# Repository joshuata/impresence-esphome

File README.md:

# Presence Sensor

An open-source, ESPHome-based room presence sensor built around the Hi-Link HLK-LD2460 mmWave radar and a Seeed Studio XIAO ESP32-S3. The base device detects human presence, even when people are sitting still, and reports it to Home Assistant. Optional add-ons extend it with ambient light and CO₂ sensing.

> **Status:** early development. Hardware and firmware are not yet finalized.

<!-- TODO: hero photo of the assembled device -->

## Features

- mmWave presence detection (HLK-LD2460)
- Native Home Assistant integration through ESPHome
- Wi-Fi setup over USB or Bluetooth (Improv), with no code editing required
- Browser-based flashing, no toolchain needed
- Over-the-air updates
- Optional add-ons:
  - Ambient light sensor
  - CO₂ sensor
- Custom PCB and 3D-printable enclosure, with source files included

## Bill of materials

### Base device

| Qty | Part | Notes |
|----:|------|-------|
| 1 | Seeed Studio XIAO ESP32-S3 | |
| 1 | Hi-Link HLK-LD2460 mmWave radar | |
| 1 | Custom PCB | See [`hardware/pcb`](hardware/pcb) |
| 1 | 3D-printed enclosure | See [`hardware/enclosure`](hardware/enclosure) |
| 1 | USB-C cable + 5 V power supply | |
| 1 | PCB parts (radar sockets, Qwiic socket, LDO, passives) | Full list in [`hardware/pcb/presence-pcb-bom.csv`](hardware/pcb/presence-pcb-bom.csv) |
| 4 | M2.5 screws + heat-set inserts | Length TBD with the case |

### Optional add-ons

| Add-on | Part | Notes |
|--------|------|-------|
| Ambient light | Adafruit VEML7700 Lux Sensor, STEMMA QT (5378) | Plugs into the Qwiic chain |
| CO₂ | Adafruit SCD-40 breakout (5187) | Plugs into the Qwiic chain |

## Building

### 1. PCB

TODO: ordering the PCB from fabrication files, assembly notes, soldering order.

### 2. Enclosure

TODO: print settings (material, layer height, supports, infill) and orientation.

### 3. Assembly

TODO: mounting the PCB, radar orientation, and installing add-ons.

## Flashing

### Option A: Browser (recommended)

TODO: link to the ESP Web Tools install page. Connect the device over USB, click **Install**, then enter your Wi-Fi credentials when prompted.

### Option B: ESPHome Dashboard / CLI

Requires ESPHome TBD or newer, the first release with the [`ld2460`](https://next.esphome.io/components/sensor/ld2460/) component.

```bash
pip install esphome
esphome run firmware/presence.yaml
```

TODO: adopting the device in the ESPHome Dashboard.

## Wi-Fi setup

TODO: Improv over serial/BLE and fallback access point instructions.

## Home Assistant

TODO: discovery, exposed entities, and suggested automations.

## Enabling add-ons

TODO: how to include the add-on packages in `firmware/presence.yaml`.

## Repository layout

| Path | Contents |
|------|----------|
| `firmware/` | ESPHome configuration and add-on packages |
| `hardware/pcb/` | Autodesk Fusion PCB design and fabrication exports |
| `hardware/enclosure/` | Autodesk Fusion enclosure design and printable files |
| `docs/` | Images, wiring diagrams, web installer |

## Made for ESPHome

This project aims to meet the [Made for ESPHome](https://esphome.io/guides/made_for_esphome/) requirements. Progress against the [checklist](https://github.com/esphome/devices.esphome.io/blob/main/.github/made-for-esphome-checklist.md) is tracked in the project issues.

## Contributing

Issues and pull requests are welcome. If you use an AI coding agent, it should follow [`AGENTS.md`](AGENTS.md).

## License

- **Firmware, software, and documentation:** [GNU General Public License v3.0 or later](LICENSE) (`GPL-3.0-or-later`).
- **Hardware designs** (everything under `hardware/`: PCB, enclosure, and their fabrication exports): [CERN Open Hardware Licence v2 – Strongly Reciprocal](LICENSE-HARDWARE) (`CERN-OHL-S-2.0`).

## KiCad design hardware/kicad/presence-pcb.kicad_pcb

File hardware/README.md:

# Hardware

The Autodesk Fusion project **Presence sensor** holds the mechanical source designs; Fusion exports are kept here so they are version controlled and usable without Fusion. The main PCB is a KiCad project in this folder (see `AGENTS.md`, Hardware).

| Path | Contents |
|------|----------|
| `fusion/` | Fusion source exports (`.f3d`; `.f3z` for designs with inserted, referenced components) |
| `kicad/` | KiCad 10 project for the main PCB: schematic, board, project symbol/footprint library and build scripts |
| `pcb/` | Fabrication outputs for the main PCB: Gerber + drill zip, BOM, JLCPCB assembly files |
| `enclosure/` | Print outputs for the case (once finalized) |

## Designs

| Design | What it is |
|--------|------------|
| `ld2460 Board` | HLK-LD2460 radar: board, headers, pins, keep-outs |
| `xiao-esp32s3` | Seeed XIAO ESP32-S3: board, pin holes, USB-C, keep-out |
| `adafruit-scd40` | Adafruit SCD-40 breakout (for later case variants) |
| `adafruit-veml7700` | Adafruit VEML7700 breakout (for later case variants) |
| `presence-skeleton` | Master layout for the radar + PCB prototype. Derives the radar and XIAO models and holds every case, PCB, mount and antenna dimension. All user parameters are Favourites so other designs can derive them |
| `presence-enclosure` | Case v1: base and press-fit cover. Derives the skeleton's parameters (`_Ref`), layout sketches and reference bodies |

## Changing dimensions

The dimensions you're likely to change are named user parameters, and most others are derived from them or from the component models. In Fusion, open `presence-skeleton` and go to **Modify → Change Parameters**. Edit the value in the *User Parameters* section, and everything that depends on it updates. Parameters ending in `_Ref` come from the component models; change those in the component design instead. The case derives from the skeleton, so changes made there flow through to it. The KiCad PCB takes its outline, holes and part positions from the same values (in `kicad/scripts/build_board.py`), so update the script and rebuild the board after changing a layout parameter.

Values most people will want to check before printing are **bold**.

### Layout

| Parameter | Value | Description |
|-----------|-------|-------------|
| `pcb_thickness` | 1.6 mm | Main PCB thickness |
| **`pcb_socket_h`** | 4.3 mm | Height of the 2.0 mm female sockets the radar plugs into. Set to the part you buy |
| `pcb_margin` | 2 mm | PCB extends this far beyond the radar outline |
| `pcb_hole_inset` | 3 mm | PCB edge to mounting-hole centre |
| `pcb_pin_protrusion` | 2 mm | Through-hole pin length below the PCB |
| `layout_gap_radar_xiao` | 3 mm | Gap between the radar outline and the top of the XIAO |
| `xiao_side_offset` | 10 mm | XIAO shifted right (toward the antenna) to leave room on the left for a right-angle USB-C plug |

### Case

| Parameter | Value | Description |
|-----------|-------|-------------|
| `case_wall` | 2 mm | Wall thickness |
| `case_corner_r` | 3 mm | Outer corner radius |
| `case_margin` | 1 mm | Clearance from the PCB edge to the inner wall |
| **`case_radome_t`** | 1.4 mm | Wall thickness in front of the radar (community reports for 24 GHz; verify with a range test) |
| **`case_radome_gap`** | 2 mm | Radar antenna face to the inside of the front wall (1–3 mm) |
| **`case_bay_h`** | 12.5 mm | Cable bay below the PCB; sized for a right-angle USB-C plug |
| **`tol_clearance`** | 0.2 mm | General clearance between printed parts; tune for your printer |

### Fasteners

| Parameter | Value | Description |
|-----------|-------|-------------|
| `screw_clear_d` | 2.7 mm | M2.5 clearance hole in the PCB |
| **`insert_hole_d`** | 3.6 mm | Heat-set insert hole diameter. Inserts vary by brand; use your supplier's recommendation |
| **`insert_hole_h`** | 4 mm | Heat-set insert hole depth |
| `insert_boss_d` | 6.5 mm | Boss diameter around each insert |

### Wall mount (keyholes)

The back has two keyholes on the vertical centreline. Any accessory, such as a wedge or stand, that presents two #8 pan-head screw heads (or printed studs of the same shape) at this spacing can hold the case.

| Parameter | Value | Description |
|-----------|-------|-------------|
| **`mount_head_d`** | 7.9 mm | #8 pan-head diameter (ASME B18.6.3 nominal; measure yours) |
| **`mount_head_h`** | 2.8 mm | #8 pan-head height (nominal; measure yours) |
| `mount_shank_d` | 4.2 mm | #8 shank diameter |
| `mount_keyhole_spacing` | 40 mm | Keyhole centre-to-centre |
| `mount_slot_len` | 8 mm | Slot length above each entry hole |

### Hinge

Not used by case v1 (press-fit cover); kept in the skeleton for later variants.

| Parameter | Value | Description |
|-----------|-------|-------------|
| **`hinge_pin_d`** | 1.75 mm | Hinge pin: a piece of 1.75 mm filament or a metal pin |
| `hinge_knuckles` | 5 | Number of hinge knuckles |
| `hinge_clearance` | 0.3 mm | Knuckle and pin clearance |

### Wi-Fi / Bluetooth antenna

The XIAO's included flexible antenna sticks flat to the inside of the right-hand side wall. Its U.FL cable makes a 180° U-bend before reaching the XIAO, to take strain off the antenna joint.

| Parameter | Value | Description |
|-----------|-------|-------------|
| `ant_len` × `ant_w` × `ant_t` | 37.5 × 17.5 × 0.25 mm | Antenna size (measured) |
| `ant_cable_len` | 60 mm | U.FL cable length (measured) |
| `ant_bend_gap` | 6 mm | Spacing of the U-bend |
| `ant_drop` | 5 mm | Antenna centre below the radar centreline |
| `xiao_ufl_from_edge`, `xiao_ufl_from_centre` | 1.72, 4.73 mm | U.FL connector position on the XIAO (from Seeed's 3D model) |

### USB cable

| Parameter | Value | Description |
|-----------|-------|-------------|
| `usb_plug_w` × `usb_plug_h` | 12 × 6.5 mm | Straight USB-C plug body (measure your cable) |
| `usb_cable_d` | 4 mm | Cable diameter |
| `usb_cable_bend_r` | 10 mm | Minimum bend radius |

### Derived values (don't edit)

| Parameter | Value | Meaning |
|-----------|-------|---------|
| `z_antenna_face` | 8.0 mm | Radar antenna face above the PCB front |
| `case_front_inner` | 10.0 mm | Inside of the front wall above the PCB front |
| `pcb_back_clear` | 6.3 mm | Space behind the PCB: the largest of pin clearance, insert depth and the depth the antenna needs |
| `case_inner_depth` | 17.9 mm | Inside depth of the case |
| `case_inner_half_w`, `case_inner_top`, `case_inner_bottom` | 27.75, 19.0, 52.455 mm | Inner case extents from the radar centre |
| `ant_path_len` | 44.2 mm | Estimated antenna cable route |
| `ant_path_slack` | 15.8 mm | Spare cable. **Must stay ≥ 0**; adjust `ant_drop` if it goes negative |

At these values the case is about 59.5 × 75.5 × 21.3 mm (W × H × D).

## Main PCB

KiCad project `kicad/presence-pcb.kicad_pro`; two layers, 53.5 × 57.955 mm, 1.6 mm. The outline, the four M2.5 holes, the radar sockets and the XIAO position come from `presence-skeleton` (radar centre = origin, PCB front facing the room). Every part is on the front; the back carries only through-hole pins and a GND pour.

### Rebuilding

```sh
cd hardware/kicad
kicad-cli sch export netlist --format kicadsexpr -o /tmp/presence.net presence-pcb.kicad_sch
"/Applications/KiCad/KiCad.app/Contents/Frameworks/Python.framework/Versions/Current/bin/python3" \
  scripts/build_board.py /tmp/presence.net      # placement, routing, pours, silkscreen
scripts/export_fab.sh                           # ERC + DRC + parity, then hardware/pcb/*
```

`build_board.py` routes with its own small grid router, so the board is reproducible from the schematic without an autorouter. The custom footprints in `presence.pretty` come from `scripts/gen_footprints.py`.

### Wiring

Nets are named after XIAO pins. These match `firmware/boards/xiao-esp32s3.yaml`.

| Net | XIAO pin | Goes to |
|-----|----------|---------|
| `D8` | D8 (TX) | LD2460 J1 pin 8, Rx2 |
| `D9` | D9 (RX) | LD2460 J1 pin 7, Tx2 |
| `D4` | D4 (SDA) | Qwiic J3 pin 3, J4 pin 3 |
| `D5` | D5 (SCL) | Qwiic J3 pin 4, J4 pin 4 |
| `5V` | 5V (VBUS) | Radar filter, Qwiic LDO, hardwired input diode |
| `RADAR_5V` | – | LD2460 JP103 pin 1, after FB1 + 22 µF + 100 nF |
| `QWIIC_3V3` | – | Qwiic J3/J4 pin 2, from the AP2112K LDO U2 |
| `GND` | GND | LD2460 pins 2 and 6, Qwiic pin 1 |
| `D0` `D1` `D3` `D6` `D7` `D10` | spare | Test pads TP1–TP6 (through-hole, wire-solderable). D2 is left unconnected: GPIO3 is an S3 strapping pin |

LD2460 pin numbers follow manual V1.1, Fig. 3. The PCB faces the module's component side, so the socket footprints are mirrored relative to that photo: on the PCB, JP103 pin 1 (5 V) is the bottom pin of the column nearest the board edge, and J1 pin 5 is the bottom pin of the inner column. **Check the first board against a module before powering it.**

### Parts

`pcb/presence-pcb-bom.csv` lists every part. `pcb/presence-pcb-bom-jlcpcb.csv` and `pcb/presence-pcb-cpl-jlcpcb.csv` are for JLCPCB assembly: they include the SMD parts, the radar sockets and the Qwiic socket, and leave out the XIAO (hand-soldered) and the DNP parts. Check the part rotations in JLCPCB's placement preview before ordering.

- **XIAO (U1):** solder it flush (castellated edges onto the pads) or on pin headers. The footprint uses the 14 edge pins only; there is no copper on the front under the XIAO's bottom pads.
- **Radar sockets (J1, J2):** 2.0 mm female, 4.3 mm tall (`pcb_socket_h`). The radar plugs in with its antennas facing out.
- **Qwiic (J3):** JST SH BM04B-SRSS-TB, top entry (the cable plugs in from the front), body centre at (-22.8, -27.5) skeleton coordinates, 3.45 mm in from the left PCB edge. The header is 4.25 mm tall and the SHR-04V-S plug housing is 5 mm tall (JST SH catalogue eSH, pp. 2–3); JST gives no mated height, so measure a real cable before finalizing the cover. J4 is the same bus on 2.54 mm pads for a soldered cable or header. Both are fed 3.3 V by a dedicated AP2112K-3.3 LDO (U2), separate from the XIAO's 3V3.
- **I²C pull-ups (R1, R2, DNP):** the Adafruit breakouts have their own. Fit 4.7 kΩ only for a breakout without pull-ups.
- **Hardwired 5 V (J5, DNP):** 2-pin 2.54 mm pads at the bottom edge for bare 5 V wires, feeding VBUS through an SS34 Schottky (D1). The XIAO's 5V pin is wired straight to its USB VBUS (XIAO ESP32S3 schematic v1.4), so D1 stops USB from back-feeding the hardwired supply, but not the reverse: a hardwired supply more than about 0.3 V above USB VBUS would feed the USB host. Unplug the hardwired supply before connecting USB to a computer.
- **Antenna side:** no copper pour within 5.5 mm of the right edge, next to the antenna on the side wall.

## Case v1 (`presence-enclosure`)

A plain box in two printed parts:

- **Base:** back wall, four side walls, M2.5 heat-set insert bosses for the PCB, two keyholes with head pockets (mount interface above), the antenna pocket on the inside of the right wall, and a U-bend guide post for the antenna cable below it.
- **Cover:** the flat radome (`case_radome_t`), with a lip that drops inside the base. The left and right lips are a press fit (`case_press_fit`) with a lead-in chamfer; the top and bottom lips only locate. The right lip stops below the antenna so it never presses on it. Pry the cover off at the seam.
- **Edges:** a small 45° chamfer (`case_edge_chamfer`) on the front and back outer edges; nothing else sticks out.
- **Cable exits:** four options, each switched on or off with a parameter (1/0). Disabled cutters are moved out of the part, so the timeline stays healthy either way.

| Exit | Parameter | Default | What it is |
|------|-----------|---------|------------|
| Bottom | `exit_bottom` | 1 | Opening for a straight USB-C plug body (`usb_plug_w` × `usb_plug_h` + clearance) through the bottom wall, in line with the XIAO's USB-C |
| Left / right | `exit_left`, `exit_right` | 0 | U-slot for the cable (`usb_cable_d`) from the wall top, at the bay floor; the cover closes it. Strain-relief ribs pinch the cable by `exit_grip` |
| Back | `exit_back` | 0 | Hole for the cable (`usb_cable_d`) through the back wall into the wall cavity, with strain-relief ribs. Thread the far end through first |

Enclosure parameters (in `presence-enclosure`, **Modify → Change Parameters**):

| Parameter | Value | Description |
|-----------|-------|-------------|
| **`case_press_fit`** | 0.1 mm | Interference per side between the cover's side lips and the base walls. Tune for your printer; 0 = slip fit |
| `case_lip_h` | 2 mm | Cover lip height into the base |
| `case_lip_t` | 1.2 mm | Cover lip thickness |
| `case_edge_chamfer` | 0.8 mm | Chamfer on the front and back outer edges. Must stay below `case_radome_t` |
| `mount_hood_roof` | 1 mm | Roof over each keyhole head pocket. Above ~1.2 mm it reaches the through-hole pins behind the PCB |
| `ant_cable_d` | 1.13 mm | U.FL pigtail coax diameter (sizes the U-bend guide post); measure yours |
| `exit_grip` | 0.4 mm | How much the strain-relief ribs pinch the cable |
| `exit_bottom`, `exit_left`, `exit_right`, `exit_back` | 1, 0, 0, 0 | Cable exit toggles (see above) |
| `case_back_z`, `case_front_z`, `case_outer_half_w` | 9.9, 11.4, 29.75 mm | Derived; don't edit |

### Printing

`enclosure/presence-enclosure.3mf` is an OrcaSlicer project with both parts in print orientation: the base on its back, the cover radome-down. Neither needs supports (the keyhole pocket roofs and the bottom exit opening are short bridges; the edge chamfers are 45°). The embedded settings:

| Setting | Value |
|---------|-------|
| Printer profile | Bambu Lab A1 0.4 nozzle (any 0.4 mm printer works; switch it in the slicer and keep the process) |
| Material | PLA (Generic PLA). PETG also works; check radar range through the radome |
| Layer height | 0.2 mm (first layer 0.2 mm) |
| Walls | 3 |
| Top / bottom layers | 5 / 4 |
| Infill | 20 % gyroid |
| Supports | Off |
| Brim | Off |

`enclosure/presence-enclosure.step` holds both parts assembled (cover closed) for anyone who wants to modify them.

### Assembly

1. Press M2.5 heat-set inserts into the four bosses.
2. Stick the antenna into its pocket, run the cable down around the guide post and back up to the XIAO's U.FL.
3. Screw the PCB onto the inserts, plug in the cable and route it out of the enabled exit.
4. Press the cover on.

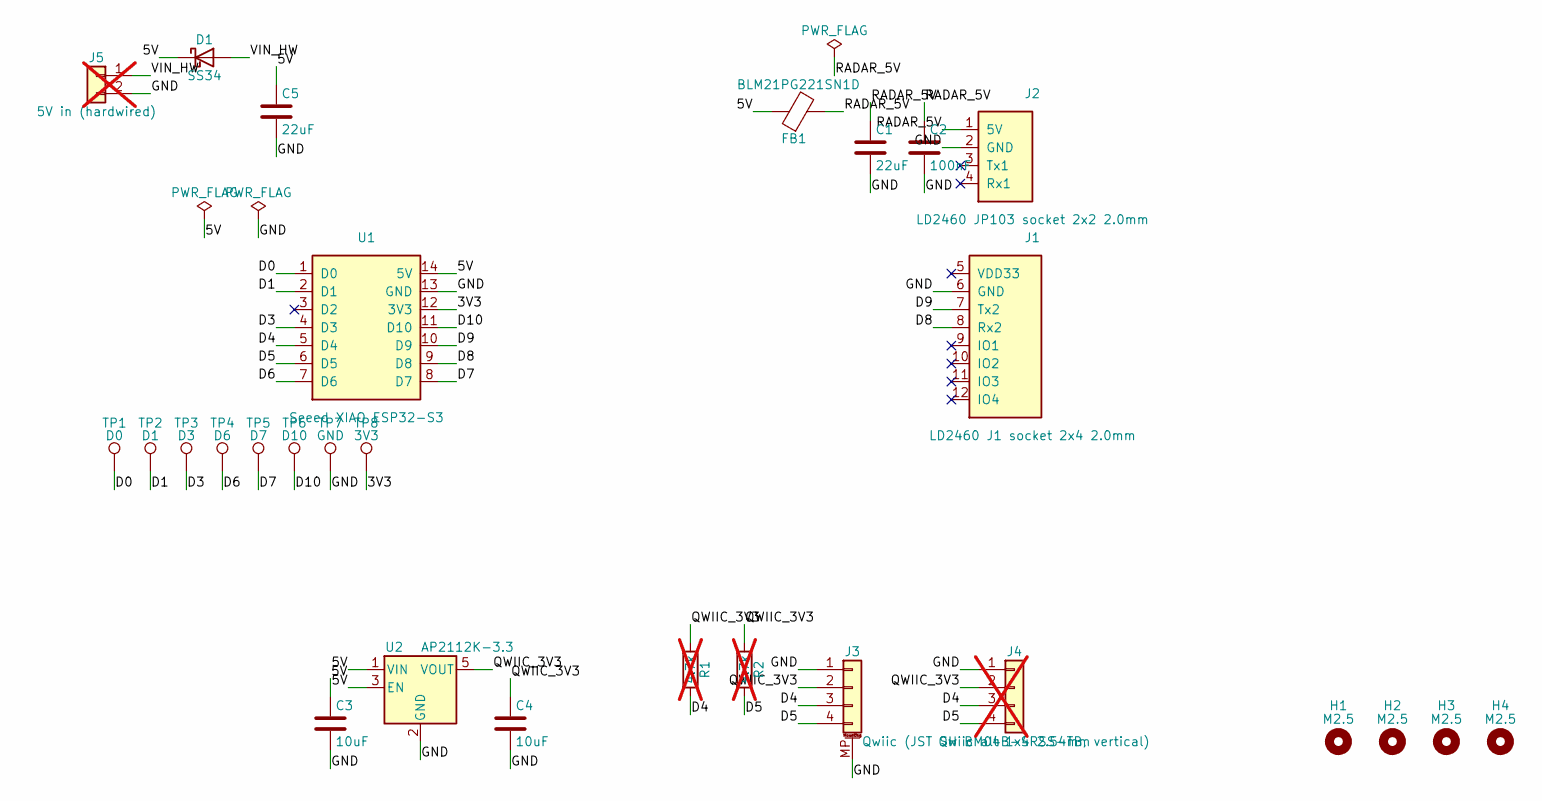
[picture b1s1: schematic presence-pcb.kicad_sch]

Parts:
C1, C5: 22uF; C_0805_2012Metric; MPN CL21A226MAQNNNE; LCSC C45783
C2: 100nF; C_0805_2012Metric; MPN CC0805KRX7R9BB104; LCSC C49678
C3, C4: 10uF; C_0805_2012Metric; MPN CL21A106KAYNNNE; LCSC C15850
D1: SS34; D_SMA; MPN SS34; LCSC C8678
FB1: BLM21PG221SN1D; L_0805_2012Metric; MPN BLM21PG221SN1D; LCSC C85840
H1, H2, H3, H4: M2.5; MountingHole_2.7mm_M2.5
J1: LD2460 J1 socket 2x4 2.0mm; LD2460_J1_Socket_2x04_P2.00mm; MPN PM200-2-04-Z-4.3; LCSC C2906072
J2: LD2460 JP103 socket 2x2 2.0mm; LD2460_JP103_Socket_2x02_P2.00mm; MPN PM200-2-02-Z-4.3; LCSC C2906070
J3: Qwiic (JST SH BM04B-SRSS-TB, vertical); JST_SH_BM04B-SRSS-TB_1x04-1MP_P1.00mm_Vertical; MPN BM04B-SRSS-TB(LF)(SN); LCSC C160390
J4: Qwiic alt 1x4 2.54mm; PinHeader_1x04_P2.54mm_Vertical; MPN 1x4 2.54 mm pin header; not fitted
J5: 5V in (hardwired); PinHeader_1x02_P2.54mm_Vertical; MPN 1x2 2.54 mm pin header or 2-pin 2.54 mm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; not fitted
R1, R2: 4.7k; R_0805_2012Metric; MPN 0805W8F4701T5E; LCSC C17673; not fitted
TP1: D0; TestPoint_THTPad_D1.5mm_Drill0.7mm
TP2: D1; TestPoint_THTPad_D1.5mm_Drill0.7mm
TP3: D3; TestPoint_THTPad_D1.5mm_Drill0.7mm
TP4: D6; TestPoint_THTPad_D1.5mm_Drill0.7mm
TP5: D7; TestPoint_THTPad_D1.5mm_Drill0.7mm
TP6: D10; TestPoint_THTPad_D1.5mm_Drill0.7mm
TP7: GND; TestPoint_THTPad_D1.5mm_Drill0.7mm
TP8: 3V3; TestPoint_THTPad_D1.5mm_Drill0.7mm
U1: Seeed XIAO ESP32-S3; XIAO_ESP32S3_EdgePins; MPN XIAO ESP32S3
U2: AP2112K-3.3; SOT-23-5; MPN AP2112K-3.3TRG1; LCSC C51118

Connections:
/3V3: TP8.1, U1.12 (3V3)
/5V: C3.1, C5.1, D1.1 (K), FB1.1, U1.14 (5V), U2.1 (VIN), U2.3 (EN)
/D0: TP1.1, U1.1 (D0)
/D1: TP2.1, U1.2 (D1)
/D3: TP3.1, U1.4 (D3)
/D4: J3.3, J4.3, R1.2, U1.5 (D4)
/D5: J3.4, J4.4, R2.2, U1.6 (D5)
/D6: TP4.1, U1.7 (D6)
/D7: TP5.1, U1.8 (D7)
/D8: J1.8 (Rx2), U1.9 (D8)
/D9: J1.7 (Tx2), U1.10 (D9)
/D10: TP6.1, U1.11 (D10)
/GND: C1.2, C2.2, C3.2, C4.2, C5.2, J1.6 (GND), J2.2 (GND), J3.1, J3.MP (MountPin), J4.1, J5.2, TP7.1, U1.13 (GND), U2.2 (GND)
/QWIIC_3V3: C4.1, J3.2, J4.2, R1.1, R2.1, U2.5 (VOUT)
/RADAR_5V: C1.1, C2.1, FB1.2, J2.1 (5V)
/VIN_HW: D1.2 (A), J5.1

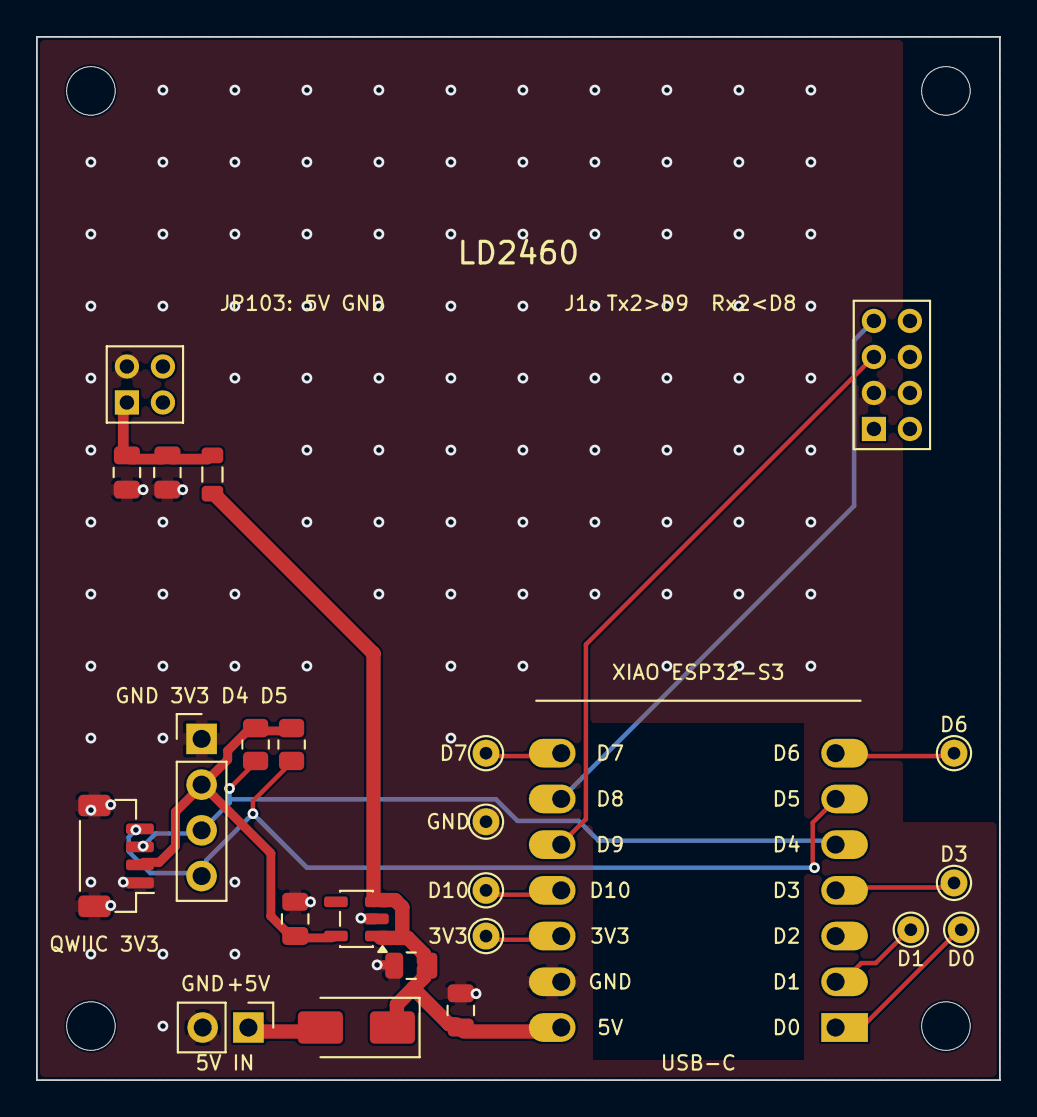
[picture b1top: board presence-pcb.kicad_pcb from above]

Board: 2 copper layers, 53.5 x 58.0 mm, 28 parts (0 on the bottom side), 16 nets.

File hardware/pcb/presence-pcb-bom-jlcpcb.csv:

Comment,Designator,Footprint,LCSC Part #
22uF,"C1,C5",C_0805_2012Metric,C45783
100nF,C2,C_0805_2012Metric,C49678
10uF,"C3,C4",C_0805_2012Metric,C15850
SS34,D1,D_SMA,C8678
BLM21PG221SN1D,FB1,L_0805_2012Metric,C85840
LD2460 J1 socket 2x4 2.0mm,J1,LD2460_J1_Socket_2x04_P2.00mm,C2906072
LD2460 JP103 socket 2x2 2.0mm,J2,LD2460_JP103_Socket_2x02_P2.00mm,C2906070
Qwiic (JST SH SM04B-SRSS-TB),J3,JST_SH_SM04B-SRSS-TB_1x04-1MP_P1.00mm_Horizontal,C160404
AP2112K-3.3,U2,SOT-23-5,C51118
